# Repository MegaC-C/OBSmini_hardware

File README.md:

# OBSmini Hardware
This repository includes all the essential PCB and 3D printing files required for the OBSmini hardware.

## PCB

The Bill of Materials (BOM) and layout take inspiration from the reference designs mentioned in the schematic. 
However, they are primarily optimized for availability and cost-effectiveness, particularly for assembly services provided by JLCPCB.

"Basic Parts" are utilized whenever tolerances permit, while "Extended Parts" are employed only when absolutely necessary.

5 PCBs cost 50€ (including parts, assembly and shipping).

[OBSmini_Schematic.pdf](https://github.com/MegaC-C/OBSmini_hardware/files/11957442/OBSmini_PCB.pdf)

## NFC Antenna PCB

This is simply a PCB antenna tuned to the NFC pins of the nRF52833.

## 3D Printed Case

Fusion 360 Project and three .stl files of OBSmini Case (Top, Spacer, Bottom).

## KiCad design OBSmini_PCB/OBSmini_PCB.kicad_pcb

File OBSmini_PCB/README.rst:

OBSmini_PCB
###########

The files needed to order at JLCPCB are in /production folder
*************************************************************

Overview
********

This is the KiCad project of the OBSmini_PCB.

The Bill of Materials (BOM) and layout take inspiration from the reference designs mentioned in the schematic. However, they are primarily optimized for availability and cost-effectiveness, particularly for assembly services provided by JLCPCB.

"Basic Parts" are utilized whenever tolerances permit, while "Extended Parts" are employed only when absolutely necessary.

5 PCBs cost 50€ (including parts, assembly and shipping).

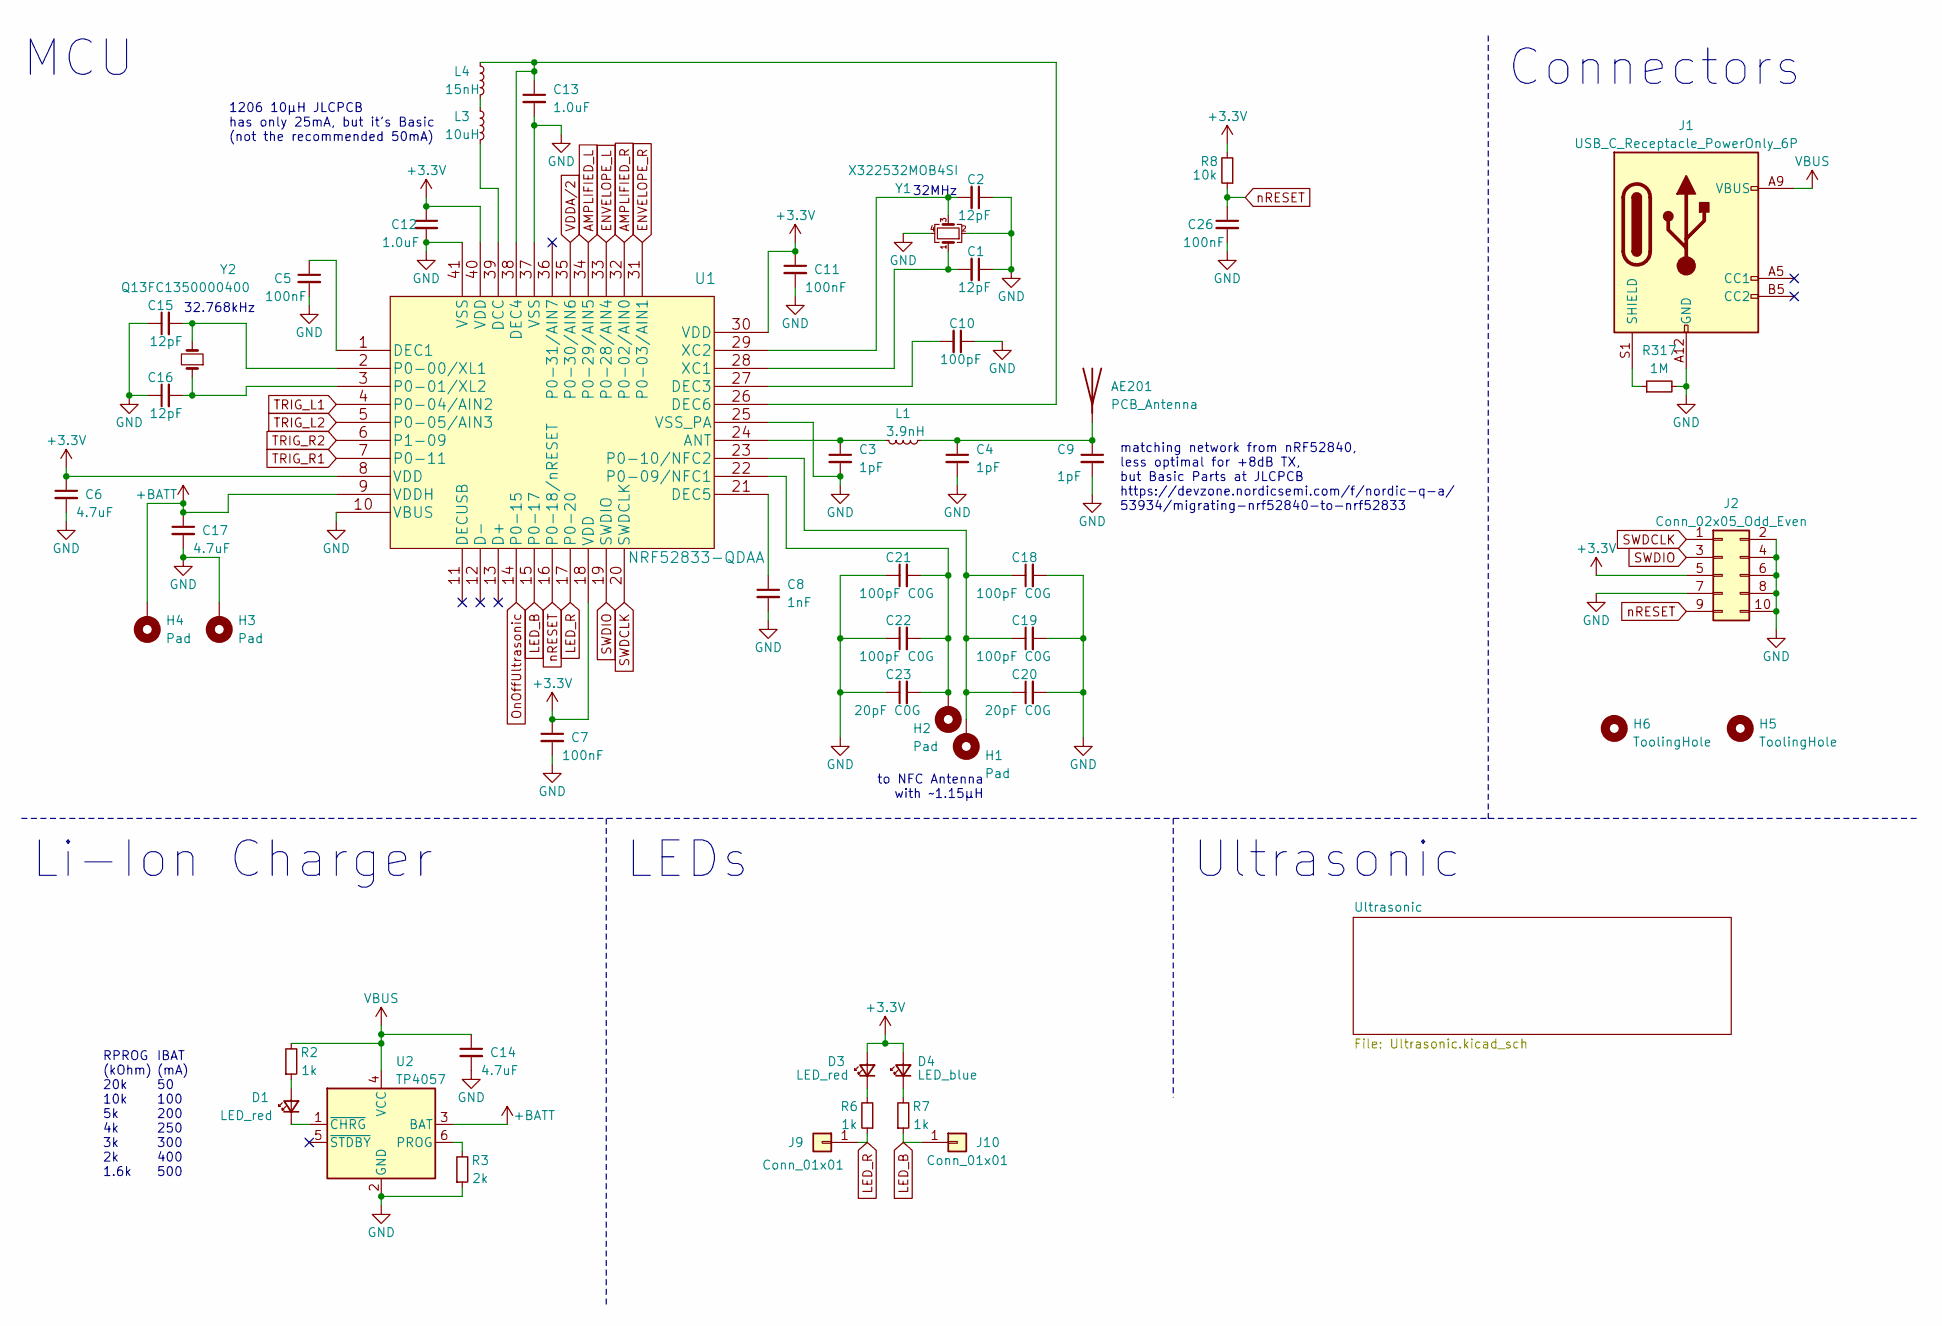
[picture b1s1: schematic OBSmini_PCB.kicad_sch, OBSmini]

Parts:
AE201: PCB_Antenna; nRF_pcbAntenna
C1, C2, C15, C16: 12pF; C_0402_1005Metric
C3, C4, C9: 1pF; C_0402_1005Metric
C5, C7, C11, C26: 100nF; C_0402_1005Metric
C6, C14, C17: 4.7uF; C_0402_1005Metric
C8: 1nF; C_0402_1005Metric
C10: 100pF; C_0402_1005Metric
C12, C13: 1.0uF; C_0402_1005Metric
C18, C19, C21, C22: 100pF C0G; C_0603_1608Metric
C20, C23: 20pF C0G; C_0402_1005Metric
D1, D3: LED_red; LED_0603_1608Metric
D4: LED_blue; LED_0603_1608Metric
H1, H2, H3, H4: Pad; SolderWirePad_1x01_SMD_1x2mm
H5, H6: ToolingHole; ToolingHoleJLCPCB
J1: USB_C_Receptacle_PowerOnly_6P; USB_C_SHOU-HAN-TYPE-C-6P
J2: Conn_02x05_Odd_Even; PinHeader_2x05_P1.27mm_Vertical
J9, J10: Conn_01x01; PinHeader_1x01_P1.27mm_Vertical
L1: 3.9nH; L_0402_1005Metric
L3: 10uH; L_1206_3216Metric
L4: 15nH; L_0402_1005Metric
R2, R6, R7: 1k; R_0402_1005Metric
R3: 2k; R_0402_1005Metric
R8: 10k; R_0402_1005Metric
R317: 1M; R_0402_1005Metric
U1: NRF52833-QDAA; NRF52833-QDAA-R7
U2: TP4057; TSOT-23-6
Y1: X322532MOB4SI; Crystal_SMD_3225-4Pin_3.2x2.5mm
Y2: Q13FC1350000400; Crystal_SMD_3215-2Pin_3.2x1.5mm

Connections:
+3.3V: C6.1, C7.1, C11.1, C12.1, D3.2 (A), D4.2 (A), J2.5, R8.2, U1.8 (VDD), U1.18 (VDD), U1.30 (VDD), U1.40 (VDD); also elsewhere on the board
+BATT: C17.1, H4.1, U1.9 (VDDH), U2.3 (BAT); also elsewhere on the board
AMPLIFIED_L: U1.34 (P0-29/AIN5); also elsewhere on the board
AMPLIFIED_R: U1.32 (P0-02/AIN0); also elsewhere on the board
ENVELOPE_L: U1.33 (P0-28/AIN4); also elsewhere on the board
ENVELOPE_R: U1.31 (P0-03/AIN1); also elsewhere on the board
LED_B: J10.1, R7.1, U1.15 (P0-17)
LED_R: J9.1, R6.1, U1.17 (P0-20)
unnamed: AE201.1 (A), C4.1, C9.1, L1.1
unnamed: D1.2 (A), R2.1
unnamed: D1.1 (K), U2.1 (~CHRG)
unnamed: D3.1 (K), R6.2
unnamed: D4.1 (K), R7.2
unnamed: L3.1, L4.2
unnamed: C3.1, L1.2, U1.24 (ANT)
unnamed: L3.2, U1.39 (DCC)
unnamed: C5.1, U1.1 (DEC1)
unnamed: C10.2, U1.27 (DEC3)
unnamed: C13.1, L4.1, U1.26 (DEC6), U1.38 (DEC4)
unnamed: C8.1, U1.21 (DEC5)
unnamed: C15.2, U1.2 (P0-00/XL1), Y2.2
unnamed: C16.2, U1.3 (P0-01/XL2), Y2.1
unnamed: C21.2, C22.2, C23.2, H2.1, U1.22 (P0-09/NFC1)
unnamed: C18.1, C19.1, C20.1, H1.1, U1.23 (P0-10/NFC2)
unnamed: C1.2, U1.28 (XC1), Y1.1
unnamed: C2.2, U1.29 (XC2), Y1.3
unnamed: R3.2, U2.6 (PROG)
OnOffUltrasonic: U1.14 (P0-15); also elsewhere on the board
SWDCLK: J2.1, U1.20 (SWDCLK)
SWDIO: J2.3, U1.19 (SWDIO)
TRIG_L1: U1.4 (P0-04/AIN2); also elsewhere on the board
TRIG_L2: U1.5 (P0-05/AIN3); also elsewhere on the board
TRIG_R1: U1.7 (P0-11); also elsewhere on the board
TRIG_R2: U1.6 (P1-09); also elsewhere on the board
VBUS: C14.1, J1.A9 (VBUS), R2.2, U2.4 (VCC)
VDDA/2: U1.35 (P0-30/AIN6); also elsewhere on the board
nRESET: C26.1, J2.9, R8.1, U1.16 (P0-18/nRESET)

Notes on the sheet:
Li-Ion Charger
32.768kHz
32MHz
matching network from nRF52840, less optimal for +8dB TX, but Basic Parts at JLCPCB https://devzone.nordicsemi.com/f/nordic-q-a/ 53934/migrating-nrf52840-to-nrf52833
LEDs
RPROG (kOhm) 20k 10k 5k 4k 3k 2k 1.6k
Connectors
MCU
to NFC Antenna with ~1.15µH
IBAT (mA) 50 100 200 250 300 400 500
1206 10µH JLCPCB has only 25mA, but it's Basic (not the recommended 50mA)
Ultrasonic

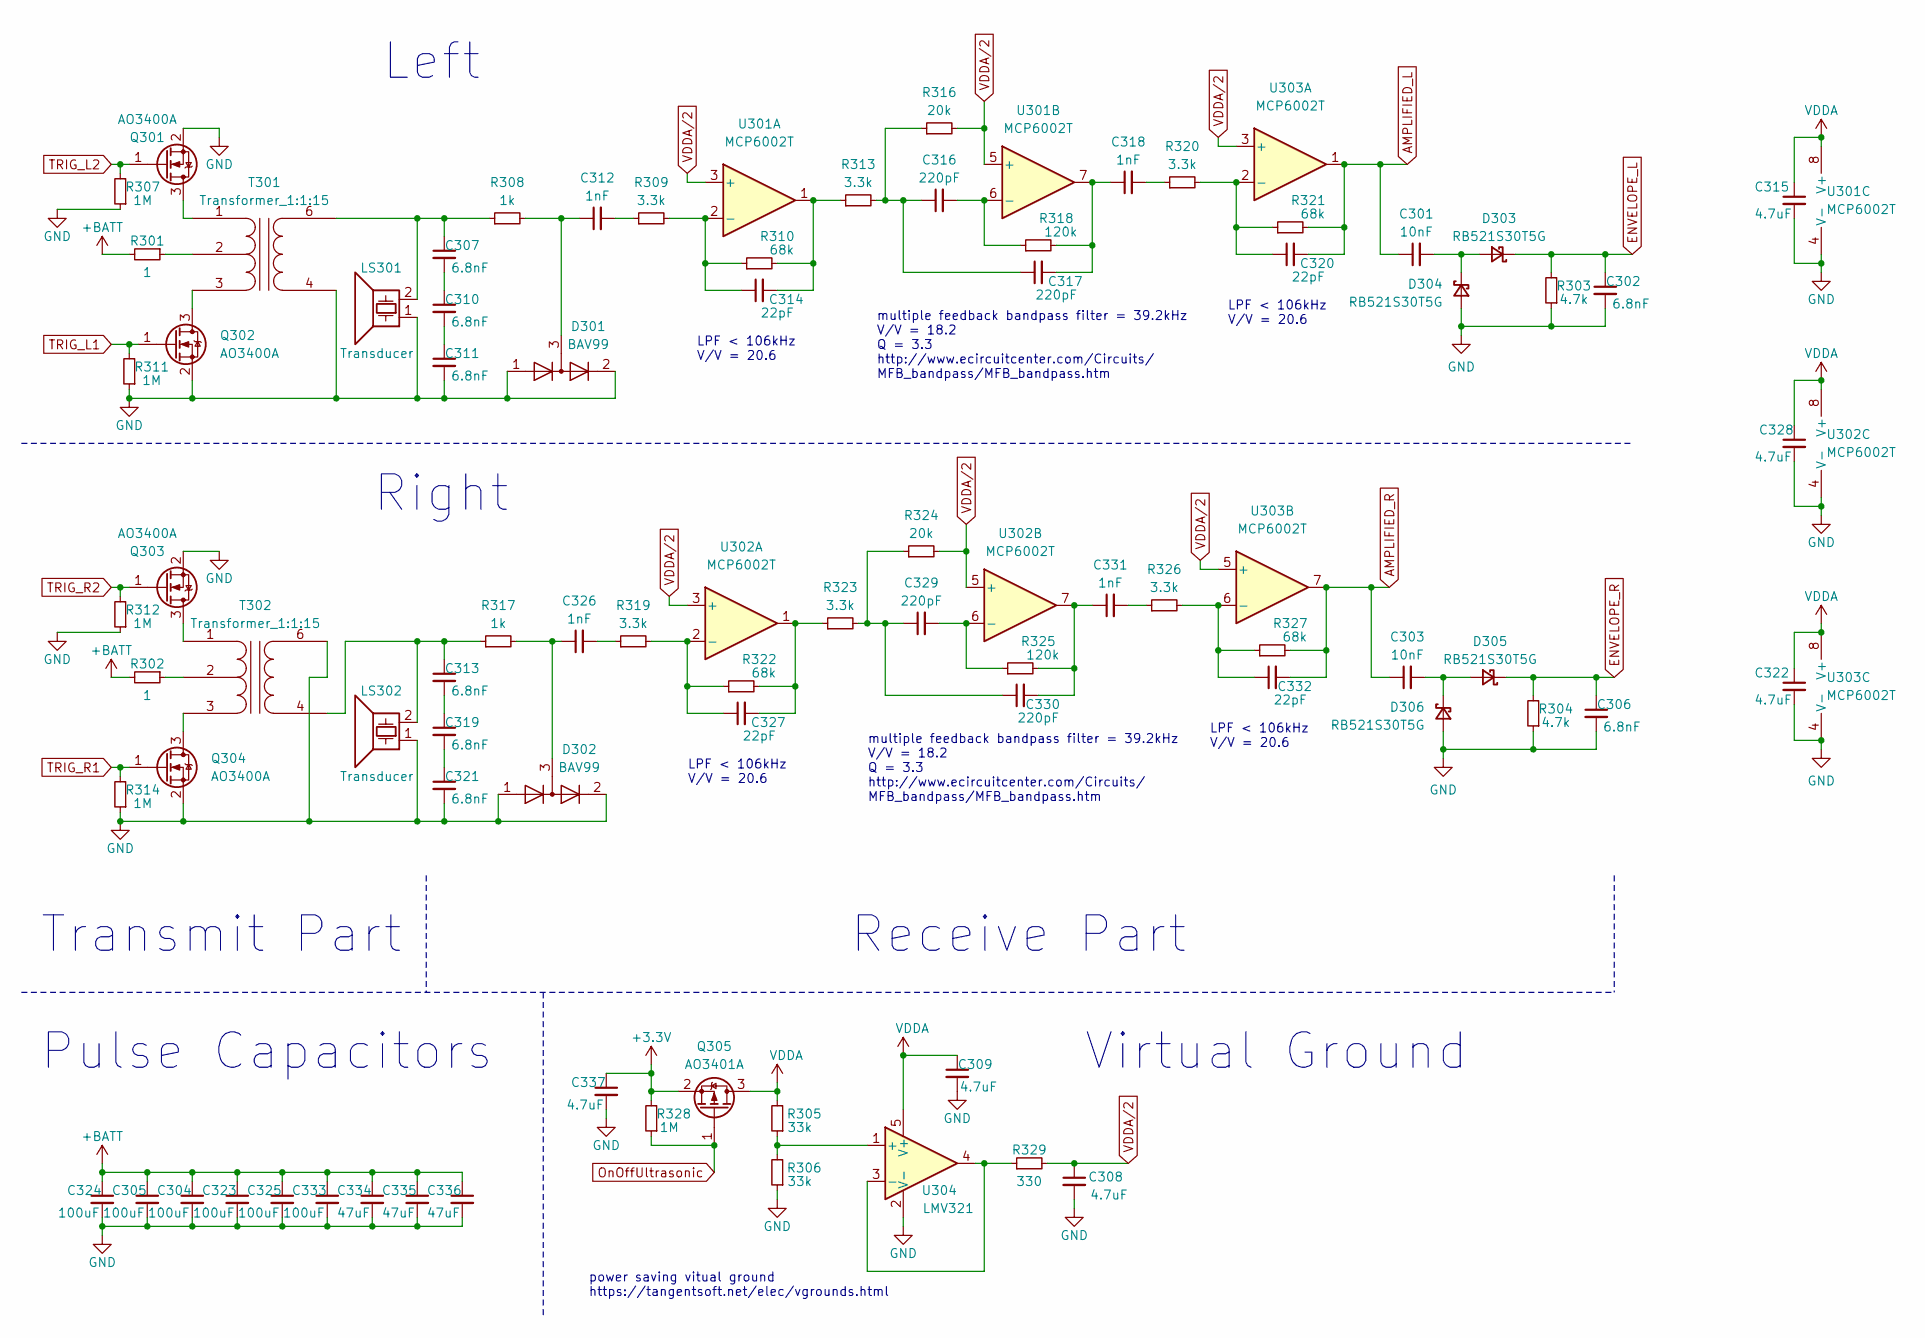
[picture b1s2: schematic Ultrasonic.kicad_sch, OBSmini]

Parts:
C301, C303: 10nF; C_0402_1005Metric
C302, C306, C307, C310, C311, C313, C319, C321: 6.8nF; C_0402_1005Metric
C304, C305, C323, C324, C325, C333: 100uF; C_1206_3216Metric
C308, C309, C315, C322, C328, C337: 4.7uF; C_0402_1005Metric
C312, C318, C326, C331: 1nF; C_0402_1005Metric
C314, C320, C327, C332: 22pF; C_0402_1005Metric
C316, C317, C329, C330: 220pF; C_0402_1005Metric
C334, C335, C336: 47uF; C_0805_2012Metric
D301, D302: BAV99; SOT-23
D303, D304, D305, D306: RB521S30T5G; D_SOD-523
LS301, LS302: Transducer; Transducer@Transformer
Q301, Q302, Q303, Q304: AO3400A; SOT-23
Q305: AO3401A; SOT-23
R301, R302: 1; R_1206_3216Metric
R303, R304: 4.7k; R_0402_1005Metric
R305, R306: 33k; R_0402_1005Metric
R307, R311, R312, R314, R328: 1M; R_0402_1005Metric
R308, R317: 1k; R_0402_1005Metric
R309, R313, R319, R320, R323, R326: 3.3k; R_0402_1005Metric
R310, R321, R322, R327: 68k; R_0402_1005Metric
R316, R324: 20k; R_0402_1005Metric
R318, R325: 120k; R_0402_1005Metric
R329: 330; R_0402_1005Metric
T301, T302: Transformer_1:1:15; B78416A2430A003
U301, U302, U303: MCP6002T; SOIC-8_3.9x4.9mm_P1.27mm
U304: LMV321; SOT-23-5

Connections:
+3.3V: C337.1, Q305.2 (S), R328.2; also elsewhere on the board
+BATT: C304.1, C305.1, C323.1, C324.1, C325.1, C333.1, C334.1, C335.1, C336.1, R301.2, R302.2; also elsewhere on the board
AMPLIFIED_L: C301.1, C320.2, R321.2, U303.1; also elsewhere on the board
AMPLIFIED_R: C303.1, C332.2, R327.2, U303.7; also elsewhere on the board
ENVELOPE_L: C302.1, D303.1 (K), R303.2; also elsewhere on the board
ENVELOPE_R: C306.1, D305.1 (K), R304.2; also elsewhere on the board
unnamed: C307.2, C310.1
unnamed: C310.2, C311.1
unnamed: C312.1, D301.3 (K), R308.2
unnamed: C312.2, R309.1
unnamed: C313.2, C319.1
unnamed: C314.2, R310.2, R313.1, U301.1
unnamed: C316.1, C317.1, R313.2, R316.1
unnamed: C317.2, C318.1, R318.2, U301.7
unnamed: C318.2, R320.1
unnamed: C319.2, C321.1
unnamed: C326.2, R319.1
unnamed: C327.2, R322.2, R323.1, U302.1
unnamed: C329.1, C330.1, R323.2, R324.1
unnamed: C330.2, C331.1, R325.2, U302.7
unnamed: C331.2, R326.1
unnamed: C301.2, D303.2 (A), D304.1 (K)
unnamed: C303.2, D305.2 (A), D306.1 (K)
unnamed: Q301.3 (D), T301.1 (PR1)
unnamed: Q302.3 (D), T301.3 (PR2)
unnamed: Q303.3 (D), T302.1 (PR1)
unnamed: Q304.3 (D), T302.3 (PR2)
unnamed: R301.1, T301.2 (PM)
unnamed: C307.1, LS301.2, R308.1, T301.6 (S2)
unnamed: R302.1, T302.2 (PM)
unnamed: C314.1, R309.2, R310.1, U301.2 (-)
unnamed: C316.2, R318.1, U301.6 (-)
unnamed: C327.1, R319.2, R322.1, U302.2 (-)
unnamed: C329.2, R325.1, U302.6 (-)
unnamed: C320.1, R320.2, R321.1, U303.2 (-)
unnamed: C332.1, R326.2, R327.1, U303.6 (-)
unnamed: R305.1, R306.2, U304.1 (+)
unnamed: R329.1, U304.3 (-), U304.4
OnOffUltrasonic: Q305.1 (G), R328.1; also elsewhere on the board
TRIG_L1: Q302.1 (G), R311.2; also elsewhere on the board
TRIG_L2: Q301.1 (G), R307.2; also elsewhere on the board
TRIG_R1: Q304.1 (G), R314.2; also elsewhere on the board
TRIG_R2: Q303.1 (G), R312.2; also elsewhere on the board
VDDA: C309.1, C315.1, C322.1, C328.1, Q305.3 (D), R305.2, U301.8 (V+), U302.8 (V+), U303.8 (V+), U304.5 (V+)
VDDA/2: C308.1, R316.2, R324.2, R329.2, U301.3 (+), U301.5 (+), U302.3 (+), U302.5 (+), U303.3 (+), U303.5 (+); also elsewhere on the board

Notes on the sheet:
Pulse Capacitors
multiple feedback bandpass filter = 39.2kHz V/V = 18.2 Q = 3.3 http://www.ecircuitcenter.com/Circuits/ MFB_bandpass/MFB_bandpass.htm
LPF < 106kHz V/V = 20.6
Receive Part
Transmit Part
Virtual Ground
Left
power saving vitual ground https://tangentsoft.net/elec/vgrounds.html
Right

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
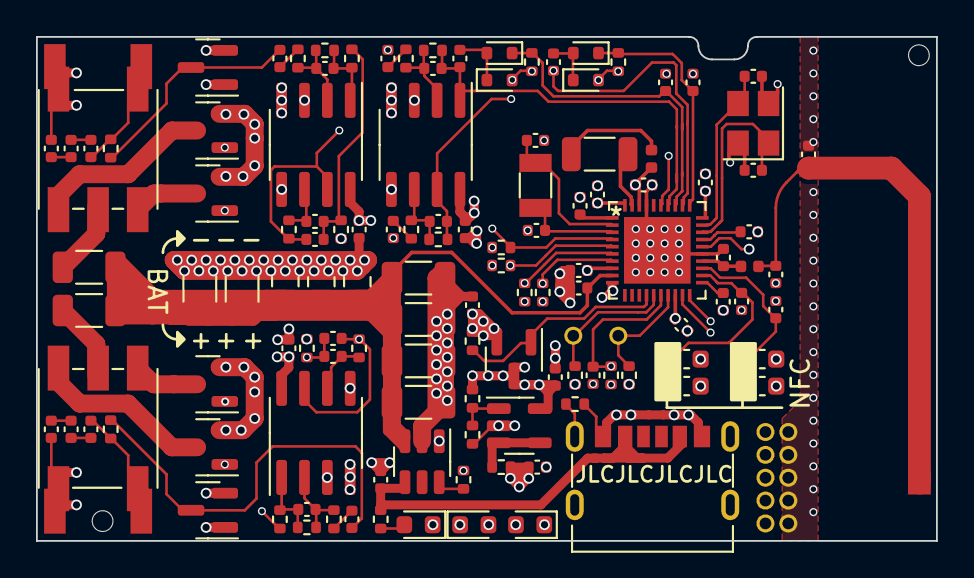
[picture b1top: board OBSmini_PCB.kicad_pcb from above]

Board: 6 copper layers, 50.0 x 28.0 mm, 135 parts (0 on the bottom side), 74 nets.

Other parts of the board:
R1: 1M; R_0402_1005Metric

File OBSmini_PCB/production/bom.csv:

Designator,Footprint,Quantity,Value,LCSC Part #
AE201,nRF_pcbAntenna,1,Antenna,
"C1, C15, C16, C2",0402,4,12pF,
C10,0402,1,100pF,
"C11, C26, C5, C7",0402,4,100nF,
"C12, C13",0402,2,1.0uF,
"C14, C17, C308, C309, C315, C322, C328, C337, C6",0402,9,4.7uF,
"C18, C19, C21, C22",0603,4,100pF C0G,
"C20, C23",0402,2,20pF C0G,
"C3, C4, C9",0402,3,1pF,
"C301, C303",0402,2,10nF,
"C302, C306, C307, C310, C311, C313, C319, C321",0402,8,6.8nF,
"C304, C305, C323, C324, C325, C333",1206,6,100uF,
"C312, C318, C326, C331, C8",0402,5,1nF,
"C314, C320, C327, C332",0402,4,22pF,
"C316, C317, C329, C330",0402,4,220pF,
"C334, C335, C336",0805,3,47uF,
"D1, D3",0603,2,LED_red,
"D301, D302",SOT-23,2,BAV99,
"D303, D304, D305, D306",D_SOD-523,4,RB521S30T5G,
D4,0603,1,LED_blue,
"H1, H2, H3, H4",SolderWirePad_1x01_SMD_1x2mm,4,Pad,
"H5, H6",ToolingHoleJLCPCB,2,MountingHole,
J1,USB_C_SHOU-HAN-TYPE-C-6P,1,USB_C_Receptacle_PowerOnly_6P,
"J10, J9",PinHeader_1x01_P1.27mm_Vertical,2,Conn_01x01,
J2,PinHeader_2x05_P1.27mm_Vertical,1,Conn_02x05_Odd_Even,
L1,0402,1,3.9nH,
L3,1206,1,10uH,
L4,0402,1,15nH,
"LS301, LS302",Transducer@Transformer,2,Transducer,
"Q301, Q302, Q303, Q304",SOT-23,4,AO3400A,
Q305,SOT-23,1,AO3401A,
"R1, R328",0402,2,1M,
"R2, R308, R317, R6, R7",0402,5,1k,
R3,0402,1,2k,
"R301, R302",1206,2,1,
"R303, R304",0402,2,4.7k,
"R305, R306",0402,2,33k,
"R309, R313, R319, R320, R323, R326",0402,6,3.3k,
"R310, R321, R322, R327",0402,4,68k,
"R316, R324",0402,2,20k,
"R318, R325",0402,2,120k,
R329,0402,1,330,
R8,0402,1,10k,
"T301, T302",B78416A2430A003,2,Transformer_1:1:15,
U1,NRF52833-QDAA-R7,1,NRF52833-QDAA,
U2,TSOT-23-6,1,TP4057,
"U301, U302, U303",SOIC-8_3.9x4.9mm_P1.27mm,3,MCP6002T,
U304,SOT-23-5,1,LMV321,
Y1,Crystal_SMD_3225-4Pin_3.2x2.5mm,1,X322532MOB4SI,
Y2,Crystal_SMD_3215-2Pin_3.2x1.5mm,1,Q13FC1350000400,

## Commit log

2023-07-03 First Commit
    must be revised
2023-07-03 added schematic
2023-07-05 added project libraries
2023-07-05 added pdf and png
2023-07-08 not sure if .f3d is the correct file
2023-07-08 added production files
2023-07-30 added window LED case
